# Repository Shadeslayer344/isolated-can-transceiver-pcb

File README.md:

# isolated-can-transceiver-pcb
Custom isolated CAN interface PCB designed in KiCad for connecting a Teensy 4.1 to the BLAZE RAYCERS solar vehicle CAN bus.

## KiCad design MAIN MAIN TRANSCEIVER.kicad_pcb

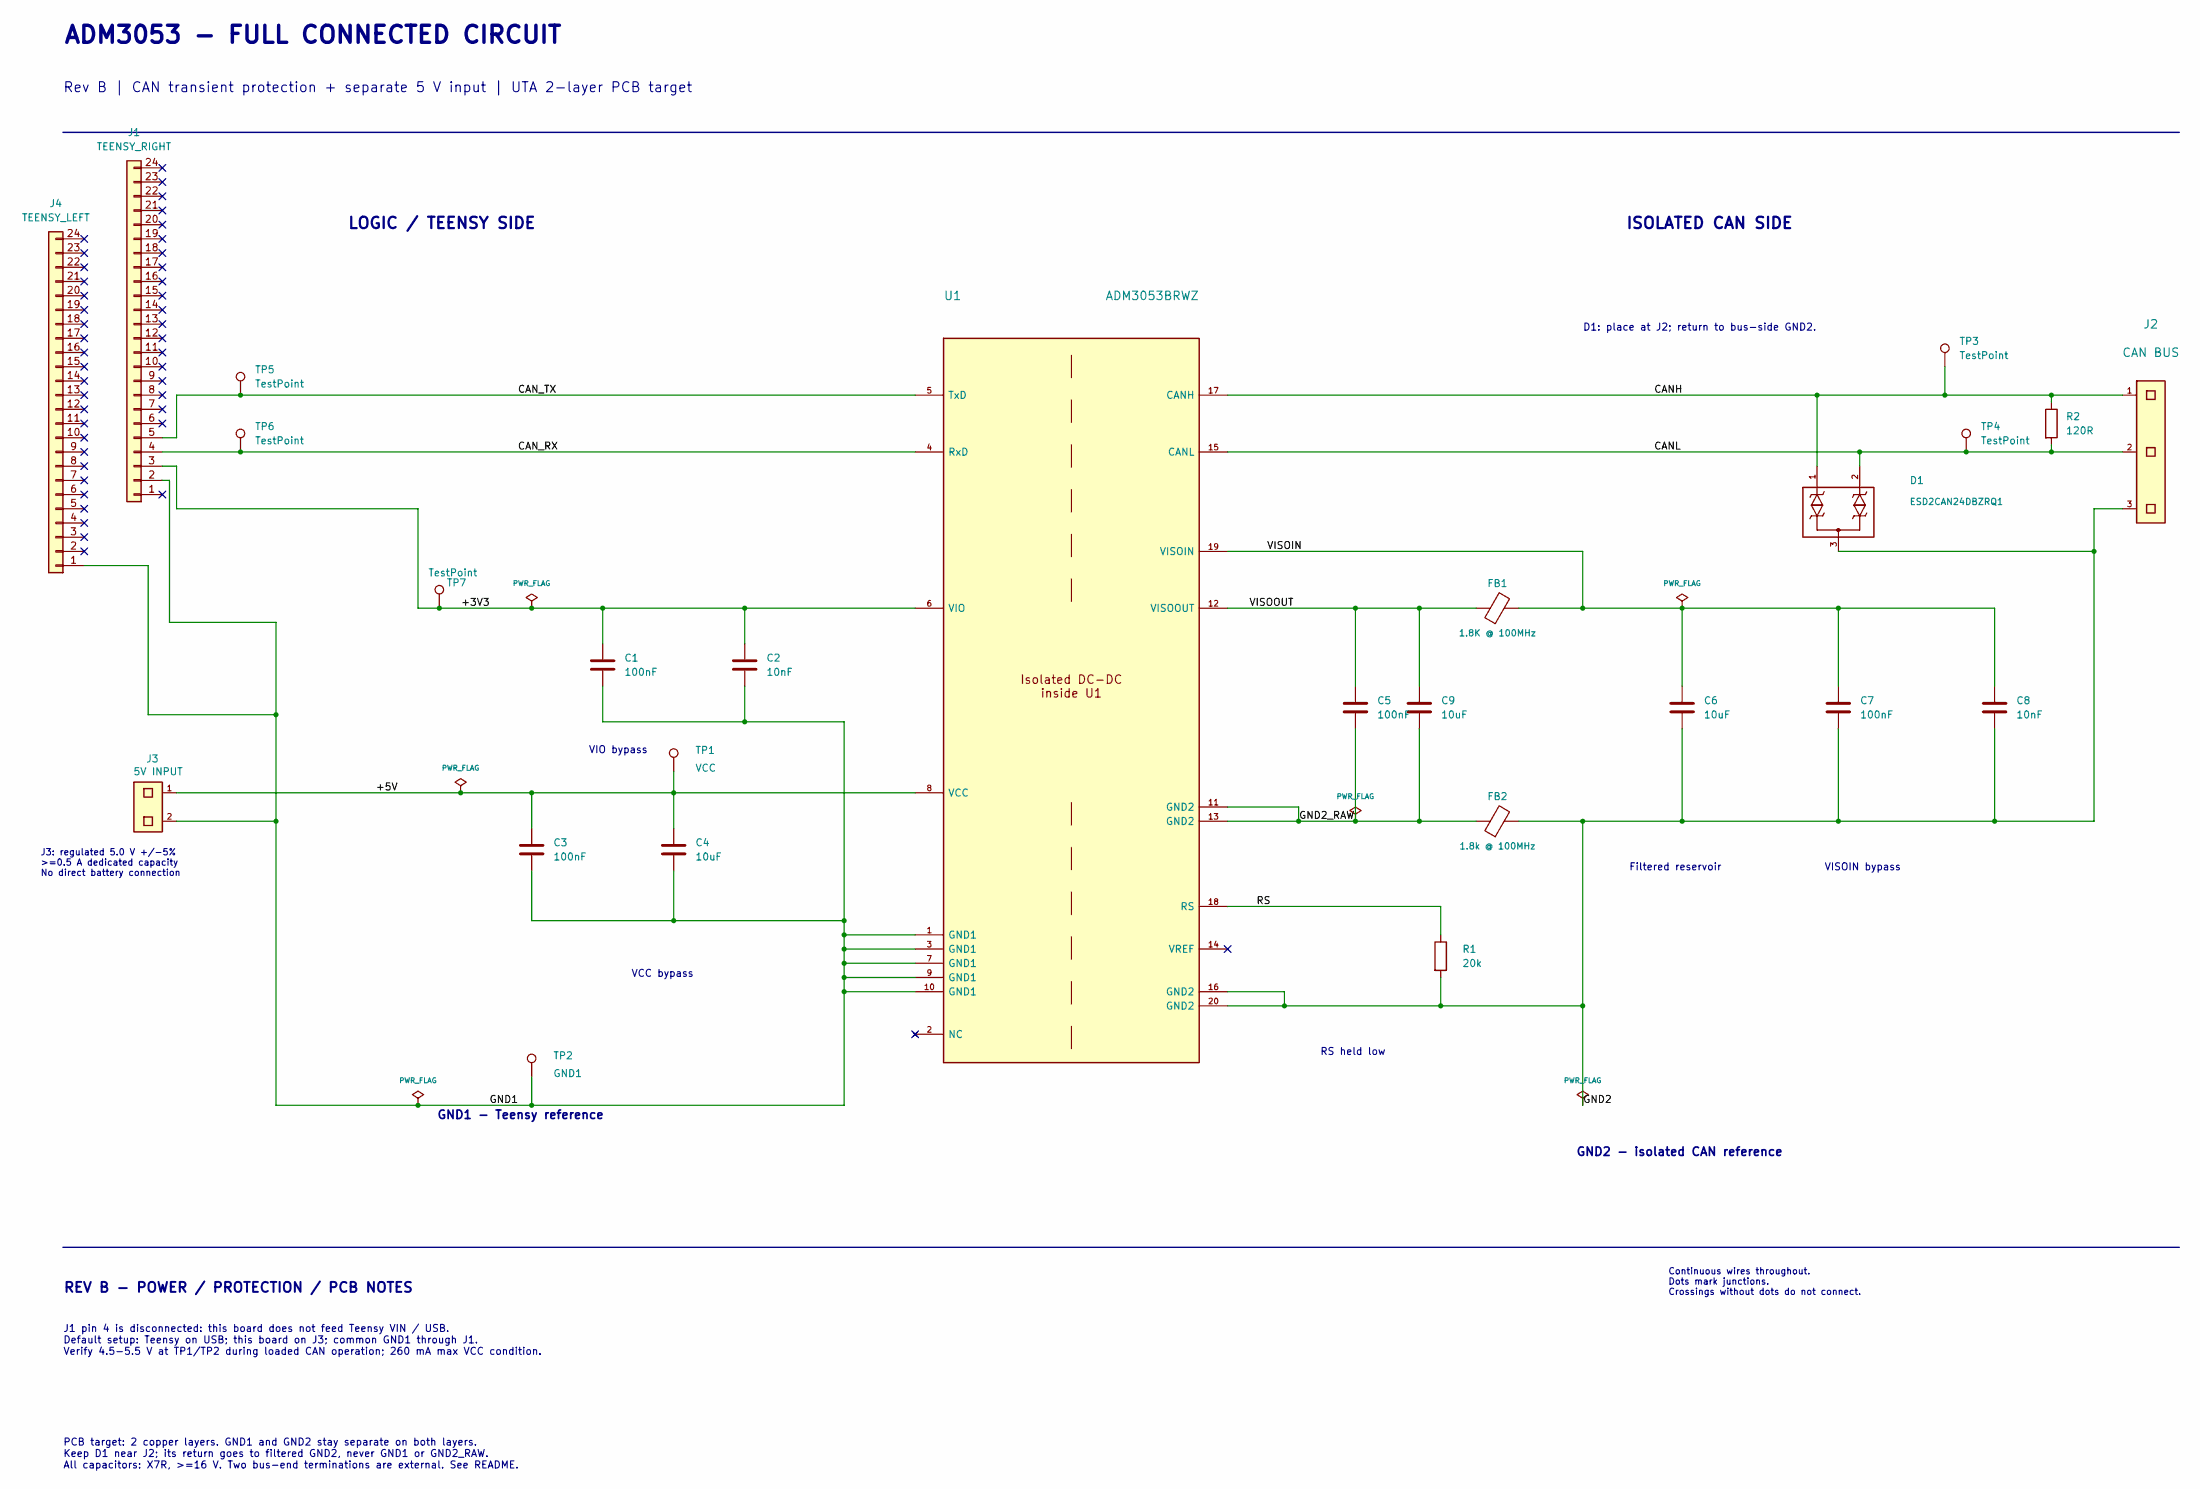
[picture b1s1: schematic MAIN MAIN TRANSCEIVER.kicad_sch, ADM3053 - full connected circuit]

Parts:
C1, C3, C5, C7: 100nF; C_0805_2012Metric; MPN C0805C104K5RACAUTO
C2: 10nF; C_0805_2012Metric
C4, C6, C9: 10uF; C_1210_3225Metric; MPN GCM32ER71E106KA57L
C8: 10nF; C_0805_2012Metric; MOUSER # 80-C0805C103K5RAUTO
D1: ESD2CAN24DBZRQ1; SOT-23; MPN ESD2CAN24DBZRQ1
FB1: 1.8K @ 100MHz; L_0805_2012Metric; MPN BLM21BD182SH1D
FB2: 1.8k @ 100MHz; L_0805_2012Metric; MPN BLM21BD182SH1D; MOUSER # 81-BLM21BD182SH1D
J1: TEENSY_RIGHT; PinSocket_1x24_P2.54mm_Vertical; MPN SSW-124-01-G-S
J2: CAN BUS; TerminalBlock_Phoenix_MKDS-1,5-3-5.08_1x03_P5.08mm_Horizont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; MPN 1715734; MOUSER # 651-1715734
J3: 5V INPUT; TerminalBlock_Phoenix_MKDS-1,5-2-5.08_1x02_P5.08mm_Horizont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; MPN 1715721; MOUSER # 651-1715721
J4: TEENSY_LEFT; PinSocket_1x24_P2.54mm_Vertical; MPN SSW-124-01-G-S
R1: 20k; R_0805_2012Metric; MPN AC0805FR-0720KL
R2: 120R; R_0805_2012Metric; MPN CRGCQ0805F120R
TP1: VCC; TestPoint_Pad_D1.5mm
TP2: GND1; TestPoint_Pad_D1.5mm
TP3, TP4, TP5, TP6, TP7: TestPoint; TestPoint_Pad_D1.5mm
U1: ADM3053BRWZ; SOIC-20W_7.5x12.8mm_P1.27mm; MPN ADM3053BRWZ

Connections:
/+3V3: C1.1, C2.1, J1.3, TP7.1 (1_1), U1.6 (VIO)
/+5V: C3.1, C4.1, J3.1, TP1.1 (1_1), U1.8 (VCC)
/CANH: D1.1 (IO1), J2.1, R2.1, TP3.1 (1_1), U1.17 (CANH)
/CANL: D1.2 (IO2), J2.2, R2.2, TP4.1 (1_1), U1.15 (CANL)
/CAN_RX: J1.4, TP6.1 (1_1), U1.4 (RxD)
/CAN_TX: J1.5, TP5.1 (1_1), U1.5 (TxD)
/GND1: C1.2, C2.2, C3.2, C4.2, J1.2, J3.2, J4.1 (Pin_1_1), TP2.1 (1_1), U1.1 (GND1), U1.3 (GND1), U1.7 (GND1), U1.9 (GND1), U1.10 (GND1)
/GND2: C6.2, C7.2, C8.2, D1.3 (GND), FB2.2, J2.3, R1.2, U1.16 (GND2), U1.20 (GND2)
/GND2_RAW: C5.2, C9.2, FB2.1, U1.11 (GND2), U1.13 (GND2)
/RS: R1.1, U1.18 (RS)
/VISOIN: C6.1, C7.1, C8.1, FB1.2, U1.19 (VISOIN)
/VISOOUT: C5.1, C9.1, FB1.1, U1.12 (VISOOUT)

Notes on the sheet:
VIO bypass
GND2 - isolated CAN reference
Rev B | CAN transient protection + separate 5 V input | UTA 2-layer PCB target
GND1 - Teensy reference
PCB target: 2 copper layers. GND1 and GND2 stay separate on both layers. Keep D1 near J2; its return goes to filtered GND2, never GND1 or GND2_RAW. All capacitors: X7R, >=16 V. Two bus-end terminations are external. See README.
ISOLATED CAN SIDE
D1: place at J2; return to bus-side GND2.
J3: regulated 5.0 V +/-5% >=0.5 A dedicated capacity No direct battery connection
Filtered reservoir
RS held low
VISOIN bypass
ADM3053 - FULL CONNECTED CIRCUIT
VCC bypass
REV B - POWER / PROTECTION / PCB NOTES
LOGIC / TEENSY SIDE
Continuous wires throughout. Dots mark junctions. Crossings without dots do not connect.
J1 pin 4 is disconnected: this board does not feed Teensy VIN / USB. Default setup: Teensy on USB; this board on J3; common GND1 through J1. Verify 4.5-5.5 V at TP1/TP2 during loaded CAN operation; 260 mA max VCC condition.

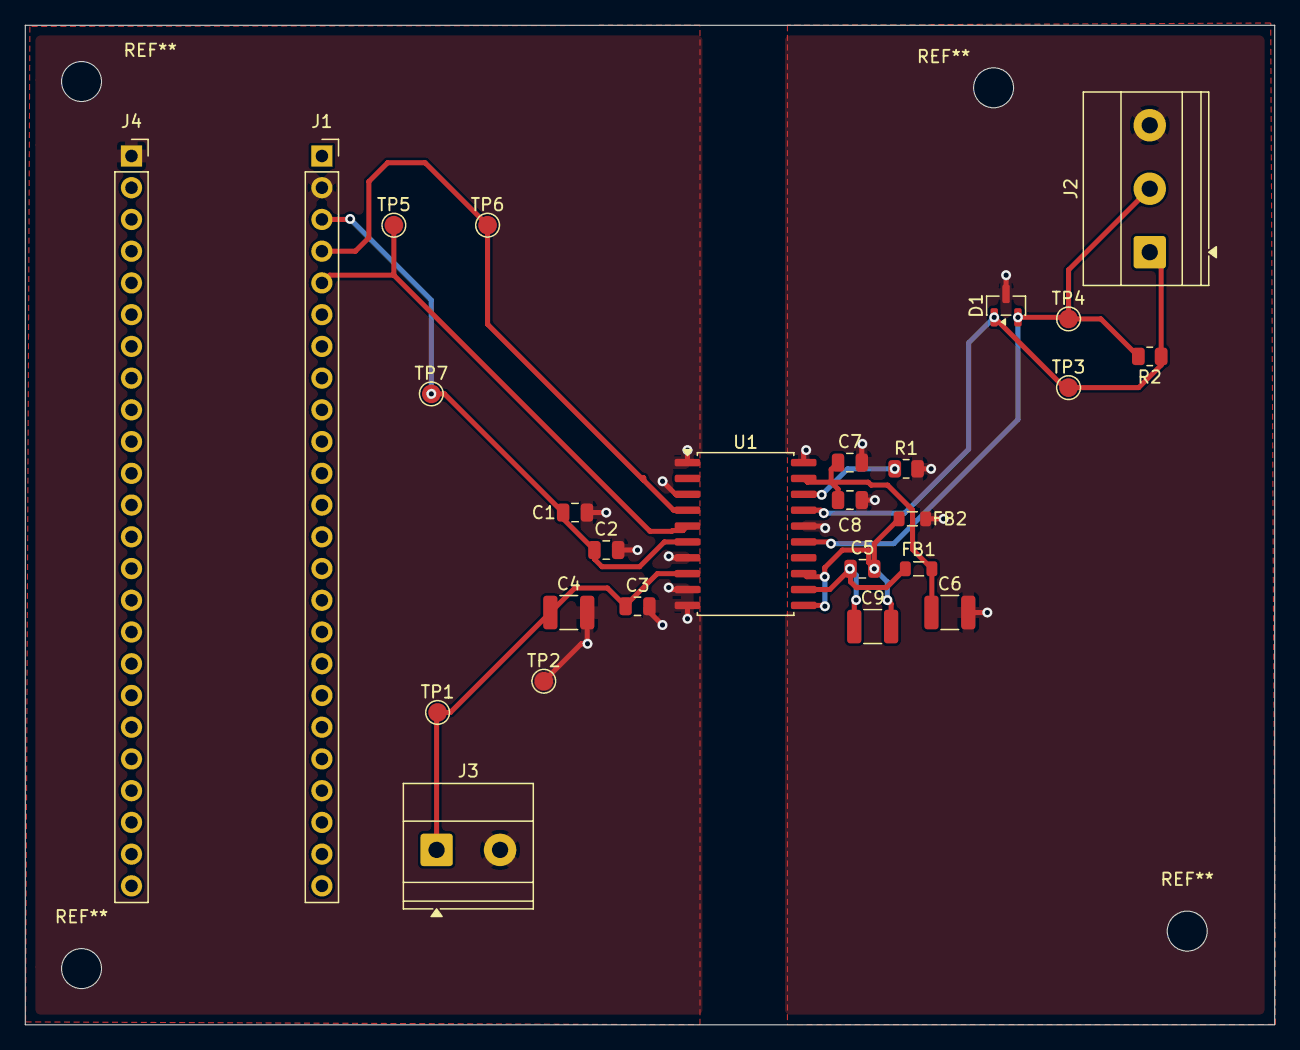
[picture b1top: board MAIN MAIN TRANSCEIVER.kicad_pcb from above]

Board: 2 copper layers, 100.0 x 80.0 mm, 26 parts (0 on the bottom side), 12 nets.
